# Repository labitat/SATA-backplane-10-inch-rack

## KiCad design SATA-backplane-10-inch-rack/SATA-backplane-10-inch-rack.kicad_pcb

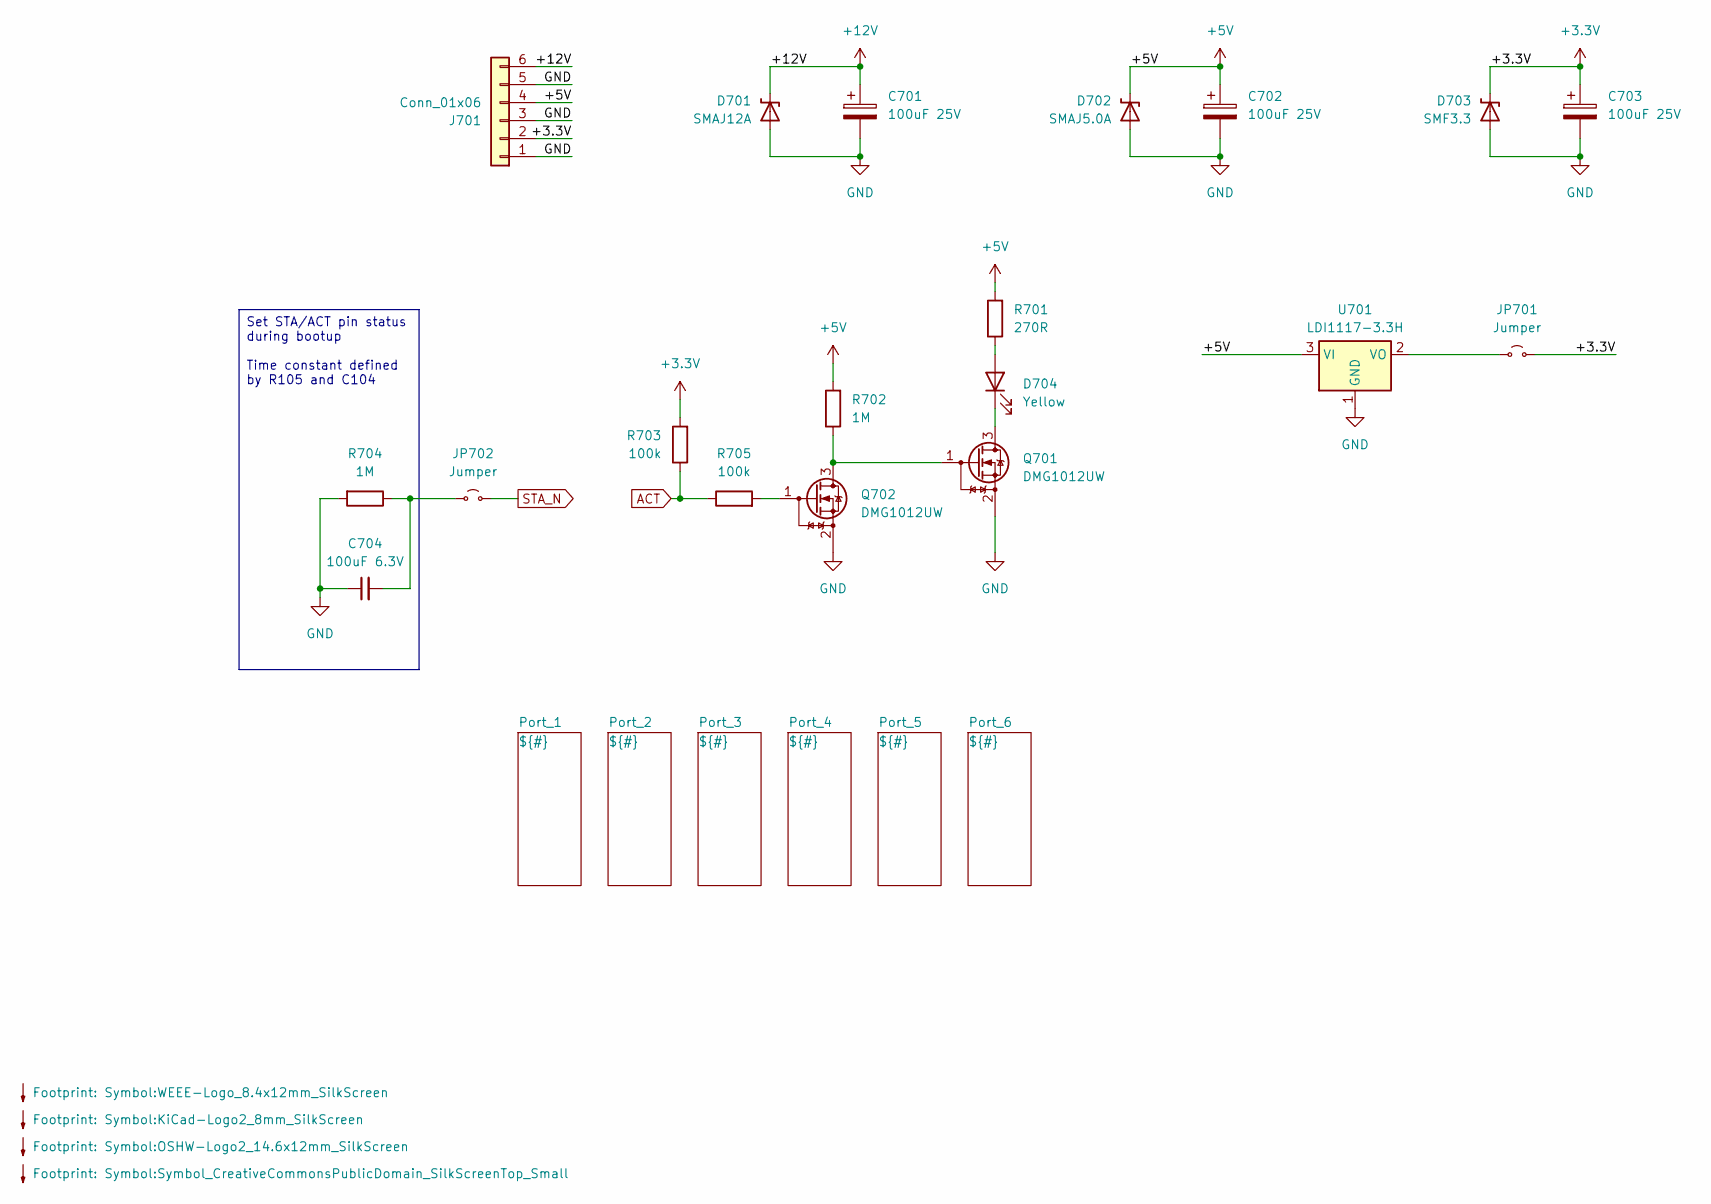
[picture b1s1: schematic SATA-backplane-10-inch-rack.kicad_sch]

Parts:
C701, C702, C703: 100uF 25V; CP_Elec_8x10.5; Mouser Part Number 667-EEE-HC1E101P
C704: 100uF 6.3V; C_1210_3225Metric_Pad1.33x2.70mm_HandSolder; Manufacturer_Part_Number JMK325BJ107MM-T; Mouser Part Number 963-JMK325BJ107MM-T
D701: SMAJ12A; D_SMA-SMB_Universal_Handsoldering; Mouser Part Number 652-SMAJ12A
D702: SMAJ5.0A; D_SMA-SMB_Universal_Handsoldering; Mouser Part Number 652-SMAJ5.0A
D703: SMF3.3; D_SMA-SMB_Universal_Handsoldering; Mouser Part Number 576-SMF3.3
D704: Yellow; LED_D3.0mm_Clear; Manufacturer_Part_Number LTL-4251N; Mouser Part Number 859-LTL-4251N
J701: Conn_01x06; TerminalBlock_Phoenix_PT-1,5-6-3.5-H_1x06_P3.50mm_Horizontal; Mouser Part Number 651-1984659
JP701, JP702: Jumper; PinHeader_1x02_P2.54mm_Horizontal; Manufacturer_Part_Number 22-28-8024; Mouser Part Number 538-22-28-8024
Q701, Q702: DMG1012UW; SOT-323_SC-70_Handsoldering; Manufacturer_Part_Number DMG1012UW-7; Mouser Part Number 621-DMG1012UW-7
R701: 270R; R_0805_2012Metric_Pad1.20x1.40mm_HandSolder; Manufacturer_Part_Number AC0805FR-07270RL; Mouser Part Number 603-AC0805FR-07270RL
R702, R704: 1M; R_0805_2012Metric_Pad1.20x1.40mm_HandSolder; Manufacturer_Part_Number AC0805FR-071ML; Mouser Part Number 603-AC0805FR-071ML
R703, R705: 100k; R_0805_2012Metric_Pad1.20x1.40mm_HandSolder; Manufacturer_Part_Number AC0805FR-07100KL; Mouser Part Number 603-AC0805FR-07100KL
SYM701: Symbol_CreativeCommonsPublicDomain_SilkScreenTop_Small
SYM702: WEEE-Logo_8.4x12mm_SilkScreen
SYM704: OSHW-Logo2_14.6x12mm_SilkScreen
SYM705: KiCad-Logo2_8mm_SilkScreen
U701: LDI1117-3.3H; SOT-223-3_TabPin2; Manufacturer_Part_Number LDI1117-3.3H; Mouser Part Number 637-LDI1117-3.3H

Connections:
+3.3V: C703.1, D703.1 (A1), J701.2, JP701.1 (A), R703.2; also elsewhere on the board
+5V: C702.1, D702.1 (A1), J701.4, R701.2, R702.2, U701.3 (VI); also elsewhere on the board
+12V: C701.1, D701.1 (A1), J701.6; also elsewhere on the board
ACT: R703.1, R705.1; also elsewhere on the board
GND: C701.2, C702.2, C703.2, C704.1, D701.2 (A2), D702.2 (A2), D703.2 (A2), J701.1, J701.3, J701.5, Q701.2 (S), Q702.2 (S), R704.2, U701.1 (GND); also elsewhere on the board
unnamed: D704.2 (A), R701.1
unnamed: D704.1 (K), Q701.3 (D)
unnamed: JP701.2 (B), U701.2 (VO)
unnamed: C704.2, JP702.2 (B), R704.1
unnamed: Q701.1 (G), Q702.3 (D), R702.1
unnamed: Q702.1 (G), R705.2
STA_N: JP702.1 (A); also elsewhere on the board

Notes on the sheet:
Set STA/ACT pin status during bootup Time constant defined by R105 and C104

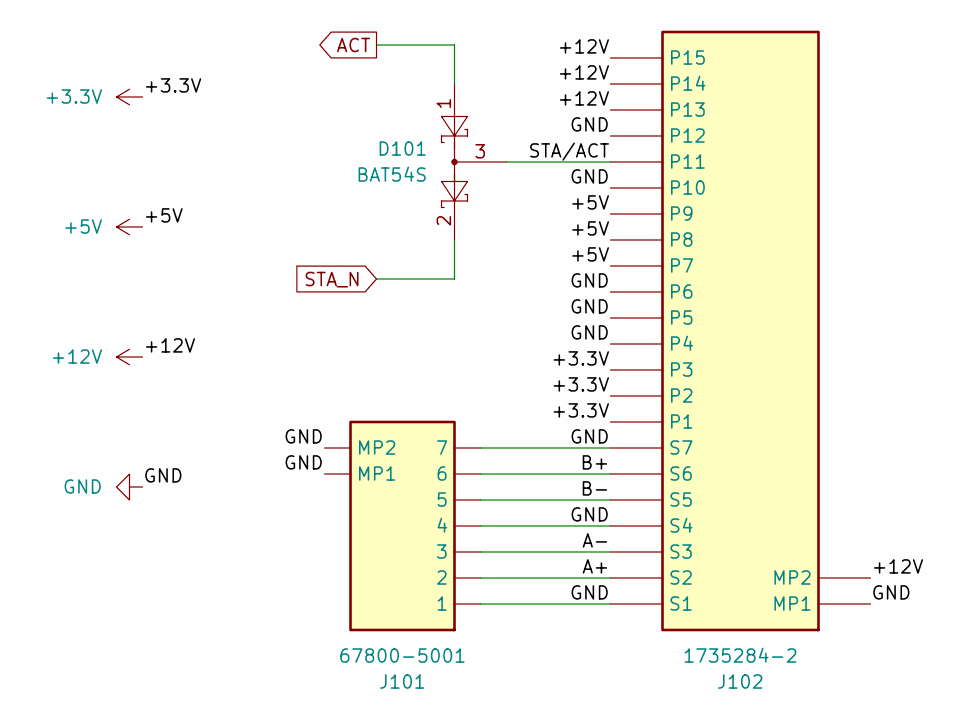
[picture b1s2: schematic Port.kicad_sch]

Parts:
D101: BAT54S; SOT-23_Handsoldering; Mouser Part Number 637-BAT54S
J101: 67800-5001; 67800-5005_2; Manufacturer_Part_Number 67800-5001; Mouser Part Number 538-67800-5001
J102: 1735284-2; 17352842; Manufacturer_Part_Number 1735284-2; Mouser Part Number 571-1735284-2

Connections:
+3.3V: J102.P1, J102.P2, J102.P3; also elsewhere on the board
+5V: J102.P7, J102.P8, J102.P9; also elsewhere on the board
+12V: J102.MP2, J102.P13, J102.P14, J102.P15; also elsewhere on the board
/Port_1/A+: J101.2, J102.S2
/Port_1/A-: J101.3, J102.S3
/Port_1/B+: J101.6, J102.S6
/Port_1/B-: J101.5, J102.S5
/Port_1/STA/ACT: D101.3 (COM), J102.P11
ACT: D101.1 (A); also elsewhere on the board
GND: J101.1, J101.4, J101.7, J101.8 (MP1), J101.9 (MP2), J102.MP1, J102.P4, J102.P5, J102.P6, J102.P10, J102.P12, J102.S1, J102.S4, J102.S7; also elsewhere on the board
STA_N: D101.2 (K); also elsewhere on the board

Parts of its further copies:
D201, D301, D401, D501, D601: BAT54S; SOT-23_Handsoldering; Mouser Part Number 637-BAT54S
J201, J301, J401, J501, J601: 67800-5001; 67800-5005_2; Manufacturer_Part_Number 67800-5001; Mouser Part Number 538-67800-5001
J202, J302, J402, J502, J602: 1735284-2; 17352842; Manufacturer_Part_Number 1735284-2; Mouser Part Number 571-1735284-2

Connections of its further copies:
+3.3V: J202.P1, J202.P2, J202.P3, J302.P1, J302.P2, J302.P3, J402.P1, J402.P2, J402.P3, J502.P1, J502.P2, J502.P3, J602.P1, J602.P2, J602.P3; also elsewhere on the board
+5V: J202.P7, J202.P8, J202.P9, J302.P7, J302.P8, J302.P9, J402.P7, J402.P8, J402.P9, J502.P7, J502.P8, J502.P9, J602.P7, J602.P8, J602.P9; also elsewhere on the board
+12V: J202.MP2, J202.P13, J202.P14, J202.P15, J302.MP2, J302.P13, J302.P14, J302.P15, J402.MP2, J402.P13, J402.P14, J402.P15, J502.MP2, J502.P13, J502.P14, J502.P15, J602.MP2, J602.P13, J602.P14, J602.P15; also elsewhere on the board
/Port_2/A+: J201.2, J202.S2
/Port_2/A-: J201.3, J202.S3
/Port_2/B+: J201.6, J202.S6
/Port_2/B-: J201.5, J202.S5
/Port_2/STA/ACT: D201.3 (COM), J202.P11
/Port_3/A+: J301.2, J302.S2
/Port_3/A-: J301.3, J302.S3
/Port_3/B+: J301.6, J302.S6
/Port_3/B-: J301.5, J302.S5
/Port_3/STA/ACT: D301.3 (COM), J302.P11
/Port_4/A+: J401.2, J402.S2
/Port_4/A-: J401.3, J402.S3
/Port_4/B+: J401.6, J402.S6
/Port_4/B-: J401.5, J402.S5
/Port_4/STA/ACT: D401.3 (COM), J402.P11
/Port_5/A+: J501.2, J502.S2
/Port_5/A-: J501.3, J502.S3
/Port_5/B+: J501.6, J502.S6
/Port_5/B-: J501.5, J502.S5
/Port_5/STA/ACT: D501.3 (COM), J502.P11
/Port_6/A+: J601.2, J602.S2
/Port_6/A-: J601.3, J602.S3
/Port_6/B+: J601.6, J602.S6
/Port_6/B-: J601.5, J602.S5
/Port_6/STA/ACT: D601.3 (COM), J602.P11
ACT: D201.1 (A), D301.1 (A), D401.1 (A), D501.1 (A), D601.1 (A); also elsewhere on the board
GND: J201.1, J201.4, J201.7, J201.8 (MP1), J201.9 (MP2), J202.MP1, J202.P4, J202.P5, J202.P6, J202.P10, J202.P12, J202.S1, J202.S4, J202.S7, J301.1, J301.4, J301.7, J301.8 (MP1), J301.9 (MP2), J302.MP1, J302.P4, J302.P5, J302.P6, J302.P10, J302.P12, J302.S1, J302.S4, J302.S7, J401.1, J401.4, J401.7, J401.8 (MP1), J401.9 (MP2), J402.MP1, J402.P4, J402.P5, J402.P6, J402.P10, J402.P12, J402.S1, J402.S4, J402.S7, J501.1, J501.4, J501.7, J501.8 (MP1), J501.9 (MP2), J502.MP1, J502.P4, J502.P5, J502.P6, J502.P10, J502.P12, J502.S1, J502.S4, J502.S7, J601.1, J601.4, J601.7, J601.8 (MP1), J601.9 (MP2), J602.MP1, J602.P4, J602.P5, J602.P6, J602.P10, J602.P12, J602.S1, J602.S4, J602.S7; also elsewhere on the board
STA_N: D201.2 (K), D301.2 (K), D401.2 (K), D501.2 (K), D601.2 (K); also elsewhere on the board

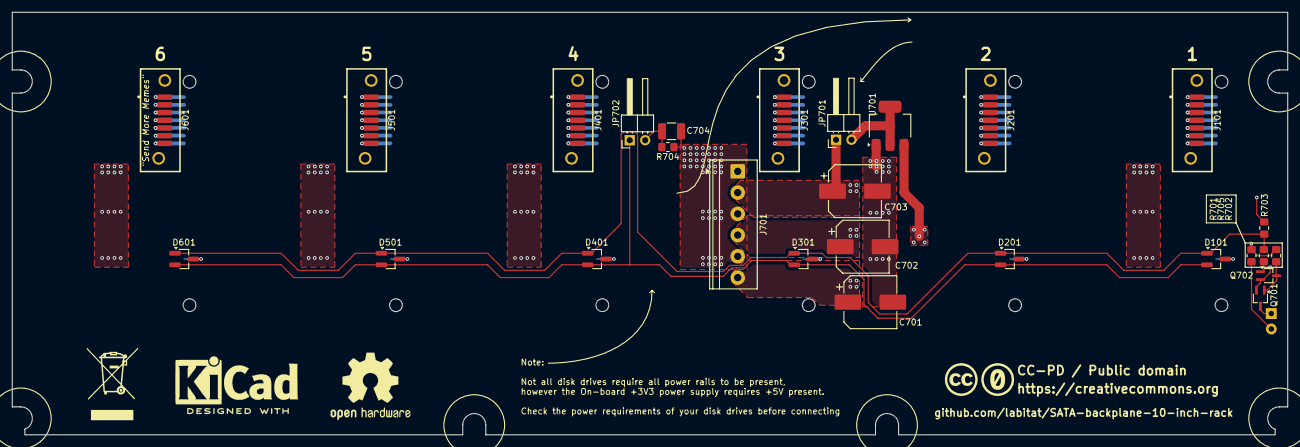
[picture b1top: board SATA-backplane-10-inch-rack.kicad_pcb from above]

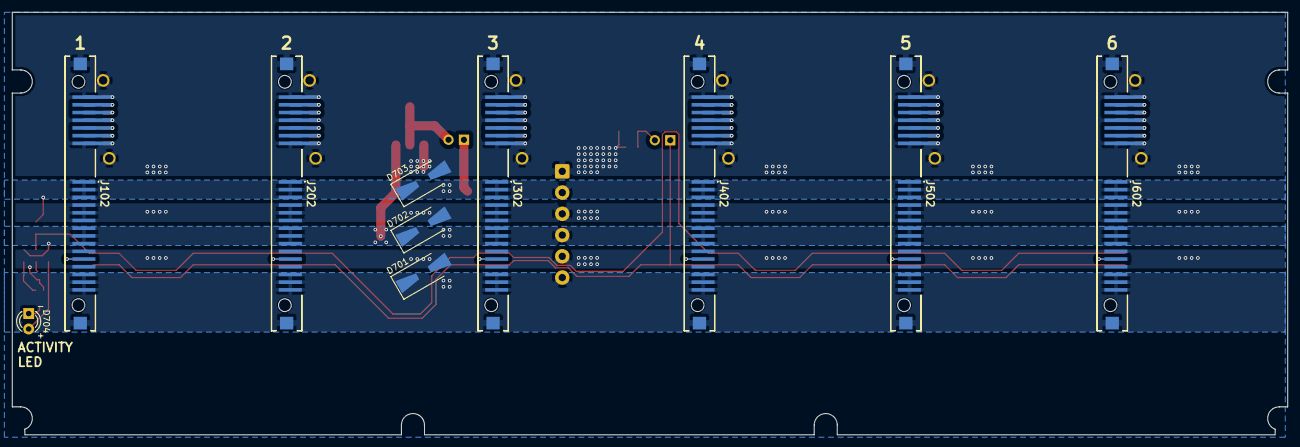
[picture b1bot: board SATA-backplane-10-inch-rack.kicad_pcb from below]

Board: 2 copper layers, 210.1 x 69.6 mm, 42 parts (10 on the bottom side), 42 nets.

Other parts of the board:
Ref**: BOM_additional_purcase_order

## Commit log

2025-02-10 Init shematic
2025-02-11 Update .gitignore to omit .zip files in repository
2025-02-11 Draw 12-module layout example
2025-02-13 More realistic layout
2025-02-14 STA/ACT implemented in layout
2025-02-21 add capacitor discharge
2025-03-26 Add 6 x 3½" HDD outline and measures
2025-03-31 Adapt to 6 x 3½" version using the multichannel tool
2025-05-06 Fix Sta/Act signal definition
2025-05-06 Align outline and mounting holes with Jeppe
2025-05-06 Prepare layout
2025-05-06 Remove .lck files
2025-05-06 Unfollow .lck files
2025-05-06 Fiddling with layout
2025-08-31 Add FreeCad files and merge with PCB STEP export
2025-09-09 Place & Route
2025-09-09 Finish layout
    Plus backport 3D into KiCAD
2025-10-01 Add drc exclusions
2025-10-02 Add text ACT to D104
2025-10-02 Update PCB from schematic
2025-10-02 Add final silkscreen items
2025-10-02 Schematic : define temporary mfg.partnumbers
2025-10-04 Set up jobsets
2025-10-04 Export
2025-10-05 Refine jobsets
2025-10-05 Rearrange reference designators numbering and silkscreen items
2025-10-05 Export (ordered at Elecrow)
2025-10-26 Generate iBom
2026-02-09 Add install logs (used RPi5 OpenMediaVault.txt)
2026-03-02 Add OpenSCAD parametric SSD cage bracket
2026-04-03 Adding disk cage for HP t740 setup
2026-04-07 add lsmd script
2026-04-07 update cages with mounting plates
2026-04-07 Adjust to final dimensions
2026-05-06 Add fan controller setup guide image

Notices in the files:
parts and their libraries:
CC-PD / Public domain
